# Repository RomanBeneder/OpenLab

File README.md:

</img>

The project OpenLab (an acronym for "Open Laboratory") is located at the Department of Embedded Systems, University of Applied Sciences Technikum Wien. It deals with the development of dedicated lecture notes, demo examples, open source measurement equipment, scripts and other course materials as well as prototype and test environments, in order to provide students low-cost, powerful measurement equipment.

The project is financed by public funds of MA23 City of Vienna, under grant number MA23-Projekt 17-08. The duration of the project is from April 2015 to March 2018.

</img>
</img>

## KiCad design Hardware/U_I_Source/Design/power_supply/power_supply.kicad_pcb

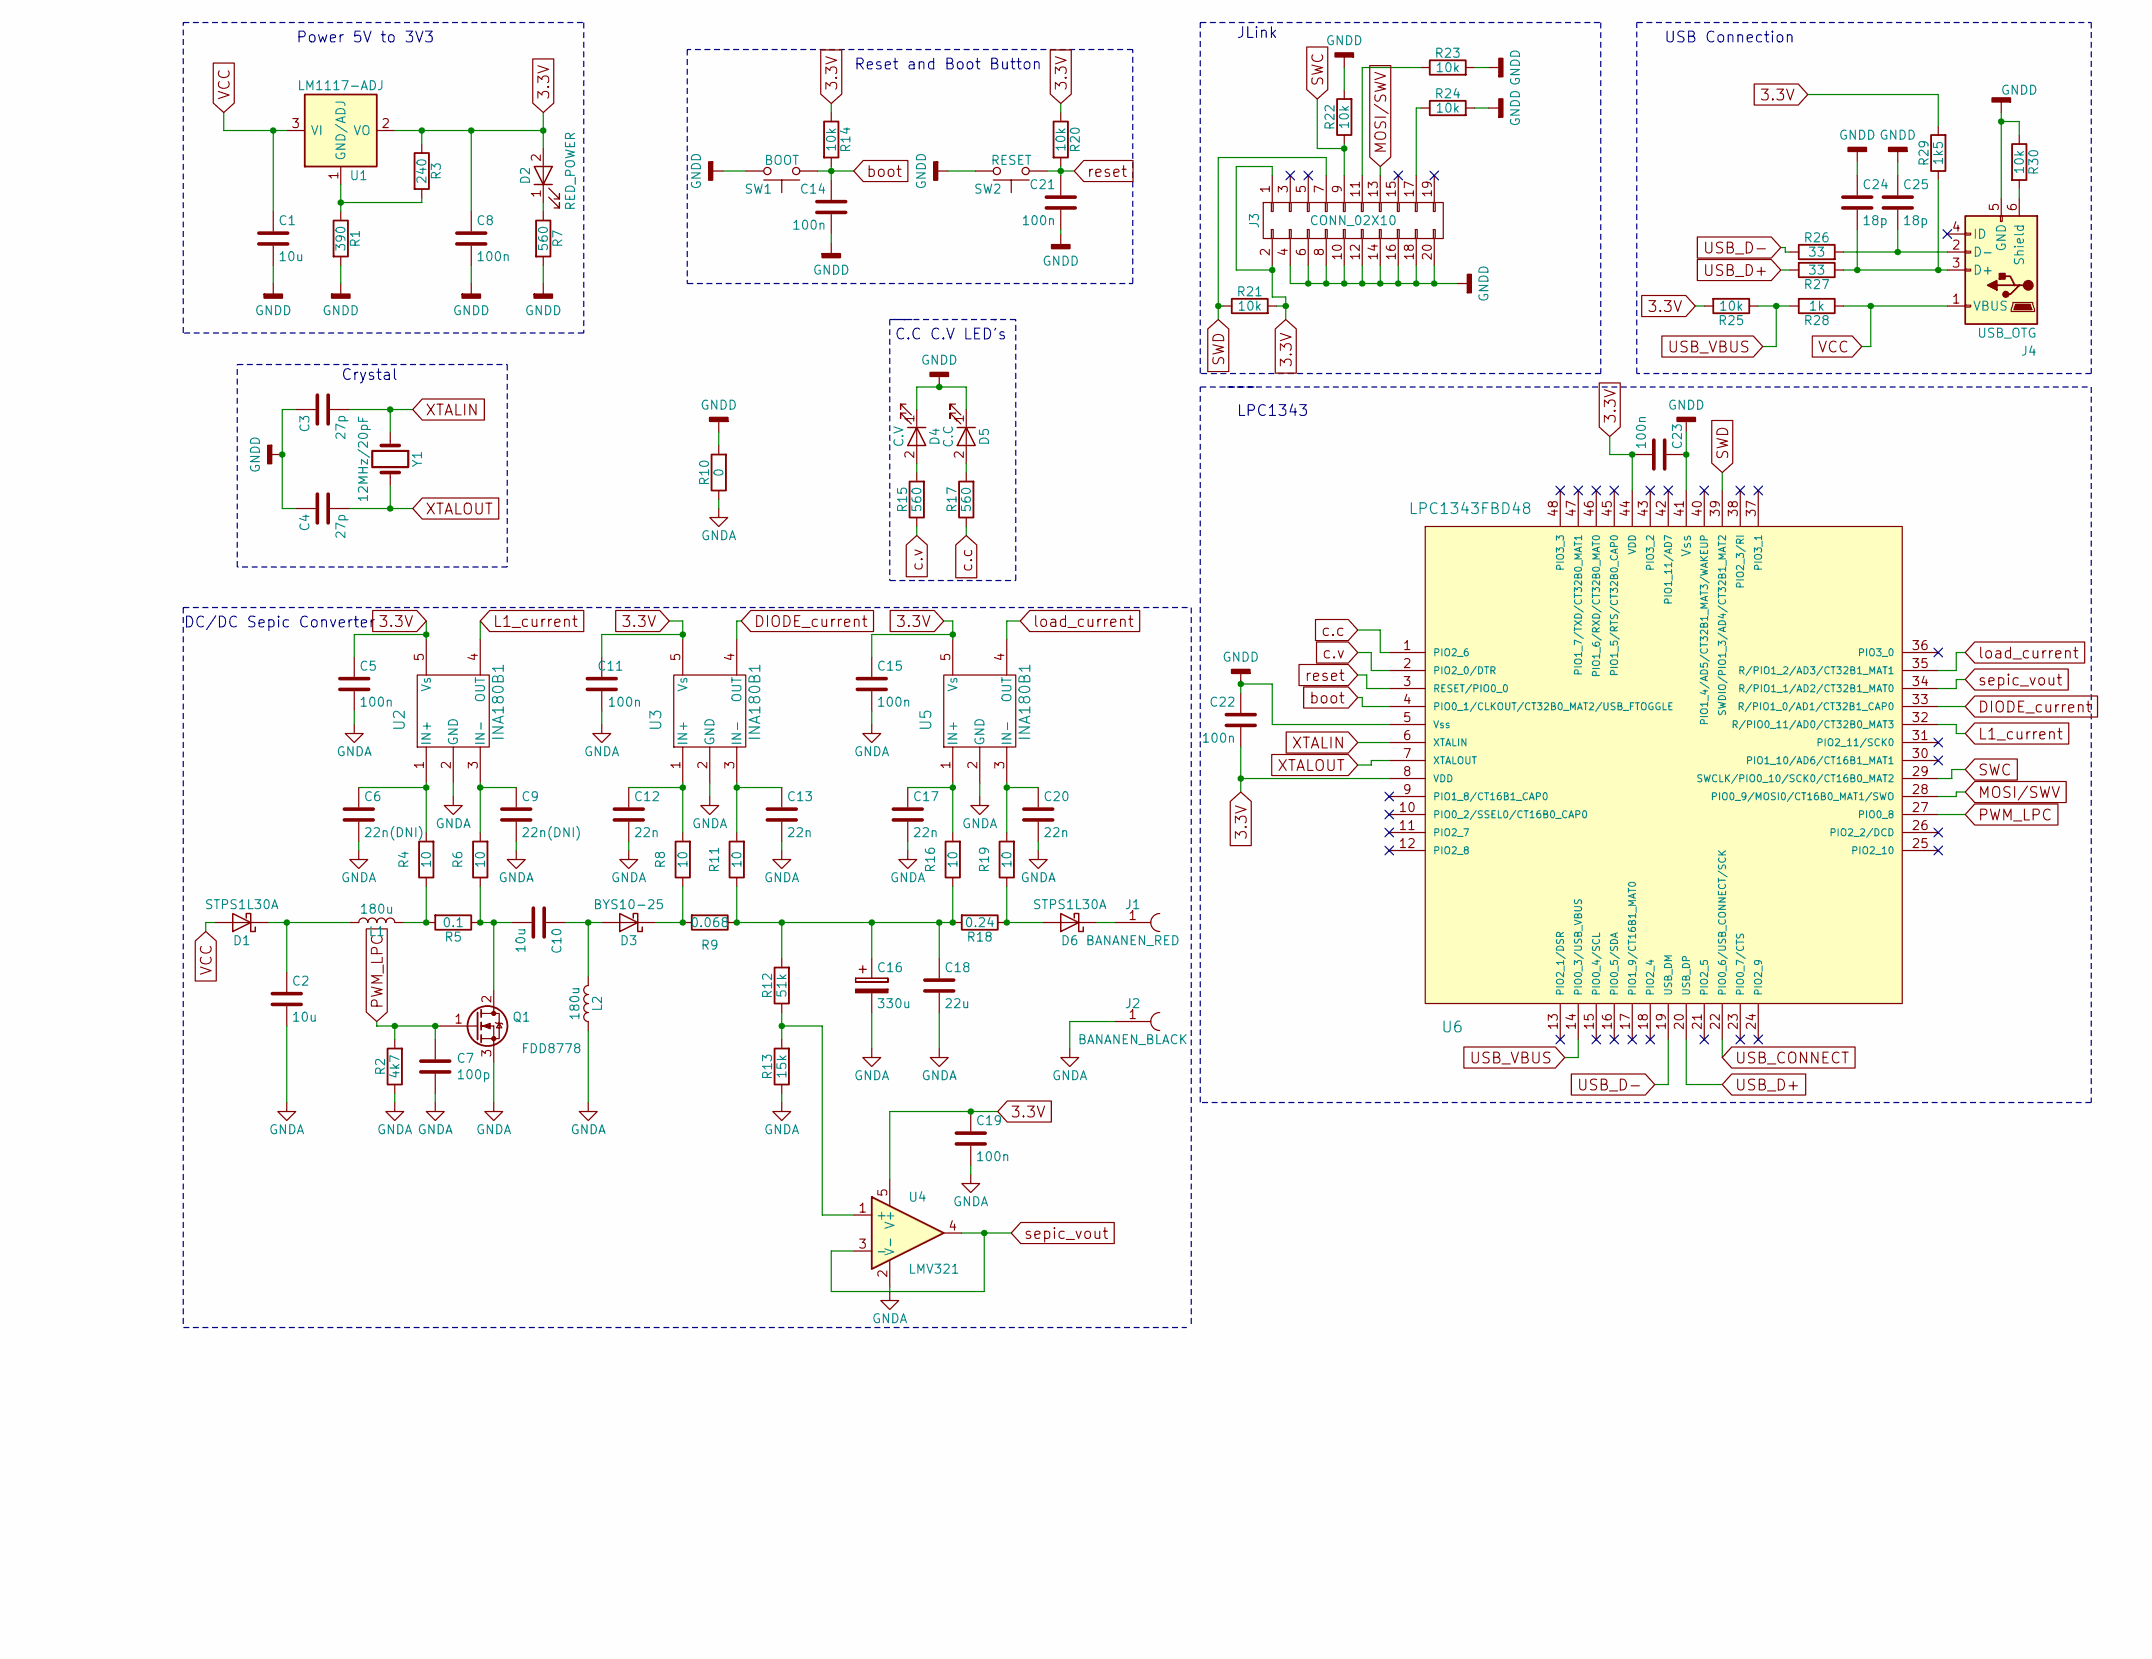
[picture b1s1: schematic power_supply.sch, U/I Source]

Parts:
C1, C2, C10: 10u; C_1206_HandSoldering
C3, C4: 27p; C_0603_HandSoldering
C5, C8, C11, C14, C15, C19, C21, C22, C23: 100n; C_0603_HandSoldering
C6, C9: 22n(DNI); C_0603
C7: 100p; C_0603_HandSoldering
C12, C13, C17, C20: 22n; C_0603
C16: 330u; CP_Elec_10x10
C18: 22u; C_1206_HandSoldering
C24, C25: 18p; C_0603_HandSoldering
D1, D6: STPS1L30A; D_SMA
D2: RED_POWER; LED_PLCC-2
D3: BYS10-25; D_SMA
D4: C.V; LED_PLCC-2
D5: C.C; LED_PLCC-2
J1: BANANEN_RED; Banana_multicomp_4mm
J2: BANANEN_BLACK; Banana_multicomp_4mm
J3: CONN_02X10; Multicomp_MC9A12-2034_2x10x2.54mm_Straight
J4: USB_OTG; USB_Micro-B_SMD
L1, L2: 180u; L_12x12mm_h8mm
Q1: FDD8778; TO-252-2
R1: 390; R_0805_HandSoldering
R2: 4k7; R_0603
R3: 240; R_0805_HandSoldering
R4, R6, R8, R11, R16, R19: 10; R_0805
R5: 0.1; R_1206_HandSoldering
R7, R15, R17: 560; R_0805_HandSoldering
R9: 0.068; R_1206_HandSoldering
R10: 0; R_0805_HandSoldering
R12: 51k; R_0805_HandSoldering
R13: 15k; R_0805_HandSoldering
R14, R20, R21, R22, R23, R24, R25, R30: 10k; R_0805_HandSoldering
R18: 0.24; R_1206_HandSoldering
R26, R27: 33; R_0805_HandSoldering
R28: 1k; R_0805_HandSoldering
R29: 1k5; R_0805_HandSoldering
SW1: BOOT; SW_SPST_KMR2
SW2: RESET; SW_SPST_KMR2
U1: LM1117-ADJ; SOT-223
U2, U3, U5: INA180B1; SOT-23-5_HandSoldering
U4: LMV321; SOT-23-5_HandSoldering
U6: LPC1343FBD48; LQFP-48_7x7mm_Pitch0.5mm
Y1: 12MHz/20pF; Crystal_SMD_HC49-SD

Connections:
3.3V: C5.1, C8.1, C11.2, C15.1, C19.1, C22.2, C23.2, D2.2 (A), J3.1, J3.2, R3.1, R14.1, R20.1, R21.2, R25.2, R29.2, U1.2 (VO), U1.4 (VO), U2.5 (Vs), U3.5 (Vs), U4.5 (V+), U5.5 (Vs), U6.8 (VDD), U6.44 (VDD)
DIODE_current: U3.4 (OUT), U6.33 (R/PIO1_0/AD1/CT32B1_CAP0)
GNDD: C1.2, C3.1, C4.1, C8.2, C14.2, C21.2, C22.1, C23.1, C24.1, C25.1, D4.1 (K), D5.1 (K), J3.4, J3.6, J3.8, J3.10, J3.12, J3.14, J3.16, J3.18, J3.20, J4.5 (GND), R1.2, R7.2, R10.2, R22.2, R23.2, R24.2, R30.1, SW1.2, SW2.2, U6.5 (Vss), U6.41 (Vss)
L1_current: U2.4 (OUT), U6.32 (R/PIO0_11/AD0/CT32B0_MAT3)
MOSI/SWV: J3.13, U6.28 (PIO0_9/MOSI0/CT16B0_MAT1/SWO)
unnamed: C2.1, D1.1 (K), L1.1
unnamed: C6.1, R4.2, U2.1 (IN+)
unnamed: C9.1, R6.2, U2.3 (IN-)
unnamed: C10.1, D3.2 (A), L2.2
unnamed: C10.2, Q1.2 (D), R5.1, R6.1
unnamed: C12.1, R8.2, U3.1 (IN+)
unnamed: C13.1, R11.2, U3.3 (IN-)
unnamed: C16.1, C18.1, R9.1, R11.1, R12.2, R16.1, R18.2
unnamed: C17.1, R16.2, U5.1 (IN+)
unnamed: C20.1, R19.2, U5.3 (IN-)
unnamed: C24.2, J4.3 (D+), R27.1, R29.1
unnamed: C25.2, J4.2 (D-), R26.2
unnamed: D2.1 (K), R7.1
unnamed: D3.1 (K), R8.1, R9.2
unnamed: D4.2 (A), R15.2
unnamed: D5.2 (A), R17.2
unnamed: D6.1 (K), J1.1
unnamed: D6.2 (A), R18.1, R19.1
unnamed: J3.11, R23.1
unnamed: J3.17, R24.1
unnamed: J4.6 (Shield), R30.2
unnamed: L1.2, R4.1, R5.2
unnamed: R1.1, R3.2, U1.1 (GND/ADJ)
unnamed: R12.1, R13.2, U4.1 (+)
PWM_LPC: C7.1, Q1.1 (G), R2.2, U6.27 (PIO0_8)
SWC: J3.9, R22.1, U6.29 (SWCLK/PIO0_10/SCK0/CT16B0_MAT2)
SWD: J3.7, R21.1, U6.39 (SWDIO/PIO1_3/AD4/CT32B1_MAT2)
USB_D+: R27.2, U6.20 (USB_DP)
USB_D-: R26.1, U6.19 (USB_DM)
USB_VBUS: R25.1, R28.2, U6.14 (PIO0_3/USB_VBUS)
VCC: C1.1, D1.2 (A), J4.1 (VBUS), R28.1, U1.3 (VI)
XTALIN: C3.2, U6.6 (XTALIN), Y1.1
XTALOUT: C4.2, U6.7 (XTALOUT), Y1.2
boot: C14.1, R14.2, SW1.1, U6.4 (PIO0_1/CLKOUT/CT32B0_MAT2/USB_FTOGGLE)
c.c: R17.1, U6.1 (PIO2_6)
c.v: R15.1, U6.2 (PIO2_0/DTR)
load_current: U5.4 (OUT), U6.35 (R/PIO1_2/AD3/CT32B1_MAT1)
reset: C21.1, R20.2, SW2.1, U6.3 (RESET/PIO0_0)

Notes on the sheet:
Power 5V to 3V3
DC/DC Sepic Converter
Crystal
Reset and Boot Button
C.C C.V LED's
JLink
USB Connection
LPC1343

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
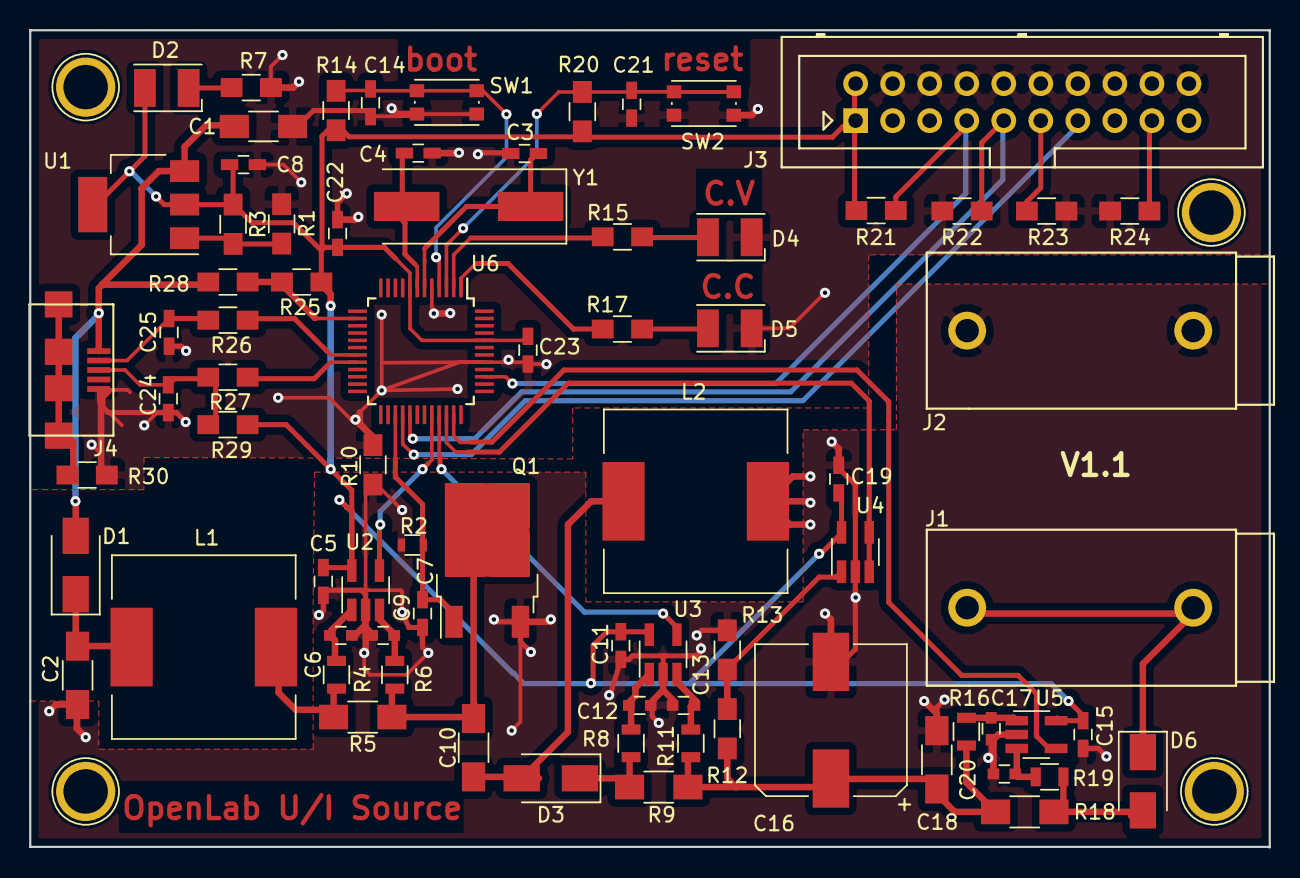
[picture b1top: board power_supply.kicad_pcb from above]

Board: 2 copper layers, 85.0 x 56.0 mm, 77 parts (0 on the bottom side), 45 nets.

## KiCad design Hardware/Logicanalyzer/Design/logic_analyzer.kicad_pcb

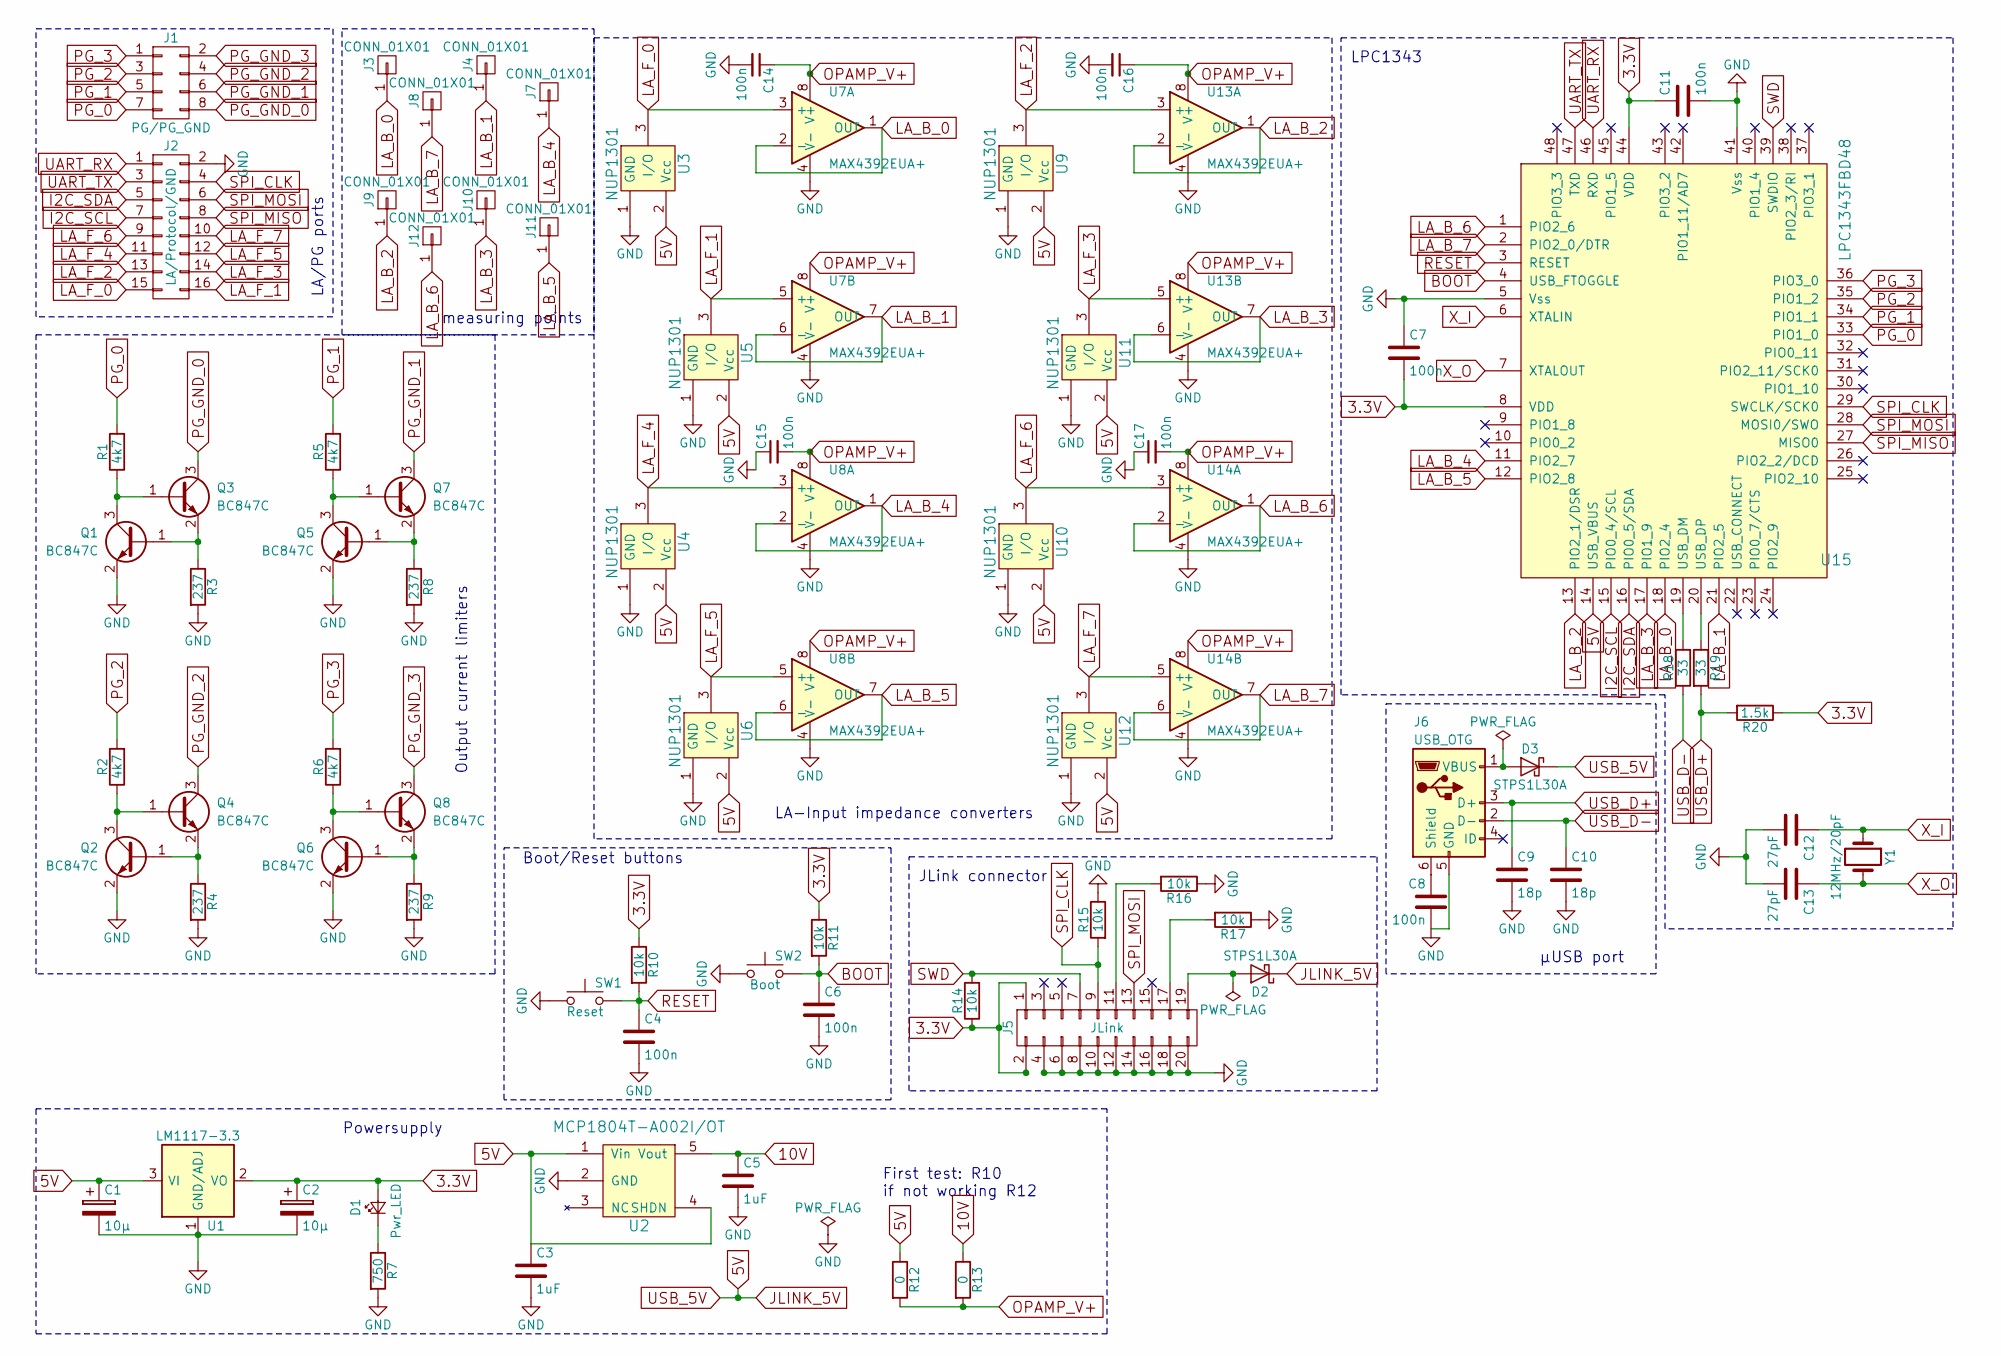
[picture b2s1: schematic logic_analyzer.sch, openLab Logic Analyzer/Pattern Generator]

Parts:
C1, C2: 10µ; C_1206
C3, C5: 1uF; C_0805
C4, C6, C7, C8, C11, C14, C15, C16, C17: 100n; C_0402
C9, C10: 18p; C_0603
C12, C13: 27pF; C_0603
D1: Pwr_LED; LED_PLCC-2
D2, D3: STPS1L30A; D_SMA
J1: PG/PG_GND; Pin_Header_Angled_2x04_Pitch2.54mm
J2: LA/Protocol/GND; Pin_Header_Angled_2x08_Pitch2.54mm
J3, J4, J7, J8, J9, J10, J11, J12: CONN_01X01; Pin_Header_Straight_1x01_Pitch2.54mm
J5: JLink; Multicomp_MC9A12-2034_2x10x2.54mm_Straight
J6: USB_OTG; USB_Micro-B_10103594-0001LF
Q1, Q2, Q3, Q4, Q5, Q6, Q7, Q8: BC847C; SOT-23
R1, R2, R5, R6: 4k7; R_0805
R3, R4, R8, R9: 237; R_0603
R7: 750; R_0603
R10, R11, R14, R15, R16, R17: 10k; R_0402
R12, R13: 0; R_2010_HandSoldering
R18, R19: 33; R_0402
R20: 1.5k; R_0805
SW1: Reset; SW_SPST_KMR2
SW2: Boot; SW_SPST_KMR2
U1: LM1117-3.3; SOT-223
U2: MCP1804T-A002I/OT; SOT-23-5
U3, U4, U5, U6, U9, U10, U11, U12: NUP1301; SOT-23
U7, U8, U13, U14: MAX4392EUA+; uMAX-8
U15: LPC1343FBD48; LQFP-48_7x7mm_Pitch0.5mm
Y1: 12MHz/20pF; Crystal_SMD_HC49-SD

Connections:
3.3V: C2.1, C7.2, C11.1, D1.2 (A), J5.1, J5.2, R10.1, R11.1, R14.1, R20.1, U1.2 (VO), U1.4 (VO), U15.8 (VDD), U15.44 (VDD)
5V: C1.1, C3.1, D2.1 (K), D3.1 (K), R12.1, U1.3 (VI), U2.1 (Vin), U2.4 (SHDN), U3.2 (Vcc), U4.2 (Vcc), U5.2 (Vcc), U6.2 (Vcc), U9.2 (Vcc), U10.2 (Vcc), U11.2 (Vcc), U12.2 (Vcc), U15.14 (USB_VBUS)
10V: C5.1, R13.1, U2.5 (Vout)
BOOT: C6.1, R11.2, SW2.2, U15.4 (USB_FTOGGLE)
GND: C1.2, C2.2, C3.2, C4.2, C5.2, C6.2, C7.1, C8.2, C9.2, C10.2, C11.2, C12.2, C13.2, C14.2, C15.1, C16.2, C17.1, J2.2, J5.4, J5.6, J5.8, J5.10, J5.12, J5.14, J5.16, J5.18, J5.20, J6.5 (GND), Q1.2 (E), Q2.2 (E), Q5.2 (E), Q6.2 (E), R3.2, R4.2, R7.2, R8.2, R9.2, R15.1, R16.1, R17.1, SW1.1, SW2.1, U1.1 (GND/ADJ), U2.2 (GND), U3.1 (GND), U4.1 (GND), U5.1 (GND), U6.1 (GND), U7.4 (V-), U8.4 (V-), U9.1 (GND), U10.1 (GND), U11.1 (GND), U12.1 (GND), U13.4 (V-), U14.4 (V-), U15.5 (Vss), U15.41 (Vss)
I2C_SCL: J2.7, U15.15 (PIO0_4/SCL)
I2C_SDA: J2.5, U15.16 (PIO0_5/SDA)
LA_B_0: J3.1, U7.1 (OUT), U7.2 (-), U15.18 (PIO2_4)
LA_B_1: J4.1, U7.6 (-), U7.7 (OUT), U15.21 (PIO2_5)
LA_B_2: J9.1, U13.1 (OUT), U13.2 (-), U15.13 (PIO2_1/DSR)
LA_B_3: J10.1, U13.6 (-), U13.7 (OUT), U15.17 (PIO1_9)
LA_B_4: J7.1, U8.1 (OUT), U8.2 (-), U15.11 (PIO2_7)
LA_B_5: J11.1, U8.6 (-), U8.7 (OUT), U15.12 (PIO2_8)
LA_B_6: J12.1, U14.1 (OUT), U14.2 (-), U15.1 (PIO2_6)
LA_B_7: J8.1, U14.6 (-), U14.7 (OUT), U15.2 (PIO2_0/DTR)
LA_F_0: J2.15, U3.3 (I/O), U7.3 (+)
LA_F_1: J2.16, U5.3 (I/O), U7.5 (+)
LA_F_2: J2.13, U9.3 (I/O), U13.3 (+)
LA_F_3: J2.14, U11.3 (I/O), U13.5 (+)
LA_F_4: J2.11, U4.3 (I/O), U8.3 (+)
LA_F_5: J2.12, U6.3 (I/O), U8.5 (+)
LA_F_6: J2.9, U10.3 (I/O), U14.3 (+)
LA_F_7: J2.10, U12.3 (I/O), U14.5 (+)
unnamed: C8.1, J6.6 (Shield)
unnamed: D1.1 (K), R7.1
unnamed: D2.2 (A), J5.19
unnamed: D3.2 (A), J6.1 (VBUS)
unnamed: J5.11, R16.2
unnamed: J5.17, R17.2
unnamed: Q1.1 (B), Q3.2 (E), R3.1
unnamed: Q1.3 (C), Q3.1 (B), R1.1
unnamed: Q2.1 (B), Q4.2 (E), R4.1
unnamed: Q2.3 (C), Q4.1 (B), R2.1
unnamed: Q5.1 (B), Q7.2 (E), R8.1
unnamed: Q5.3 (C), Q7.1 (B), R5.1
unnamed: Q6.1 (B), Q8.2 (E), R9.1
unnamed: Q6.3 (C), Q8.1 (B), R6.1
unnamed: R18.2, U15.19 (USB_DM)
unnamed: R19.1, U15.20 (USB_DP)
OPAMP_V+: C14.1, C15.2, C16.1, C17.2, R12.2, R13.2, U7.8 (V+), U8.8 (V+), U13.8 (V+), U14.8 (V+)
PG_0: J1.7, R1.2, U15.33 (PIO1_0)
PG_1: J1.5, R5.2, U15.34 (PIO1_1)
PG_2: J1.3, R2.2, U15.35 (PIO1_2)
PG_3: J1.1, R6.2, U15.36 (PIO3_0)
PG_GND_0: J1.8, Q3.3 (C)
PG_GND_1: J1.6, Q7.3 (C)
PG_GND_2: J1.4, Q4.3 (C)
PG_GND_3: J1.2, Q8.3 (C)
RESET: C4.1, R10.2, SW1.2, U15.3 (RESET)
SPI_CLK: J2.4, J5.9, R15.2, U15.29 (SWCLK/SCK0)
SPI_MISO: J2.8, U15.27 (MISO0)
SPI_MOSI: J2.6, J5.13, U15.28 (MOSI0/SWO)
SWD: J5.7, R14.2, U15.39 (SWDIO)
UART_RX: J2.1, U15.46 (RXD)
UART_TX: J2.3, U15.47 (TXD)
USB_D+: C9.1, J6.3 (D+), R19.2, R20.2
USB_D-: C10.1, J6.2 (D-), R18.1
X_I: C12.1, U15.6 (XTALIN), Y1.1
X_O: C13.1, U15.7 (XTALOUT), Y1.2

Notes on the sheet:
First test: R10 if not working R12
LPC1343
JLink connector
LA-Input impedance converters
µUSB port
LA/PG ports
Output current limiters
Powersupply
Boot/Reset buttons
measuring points

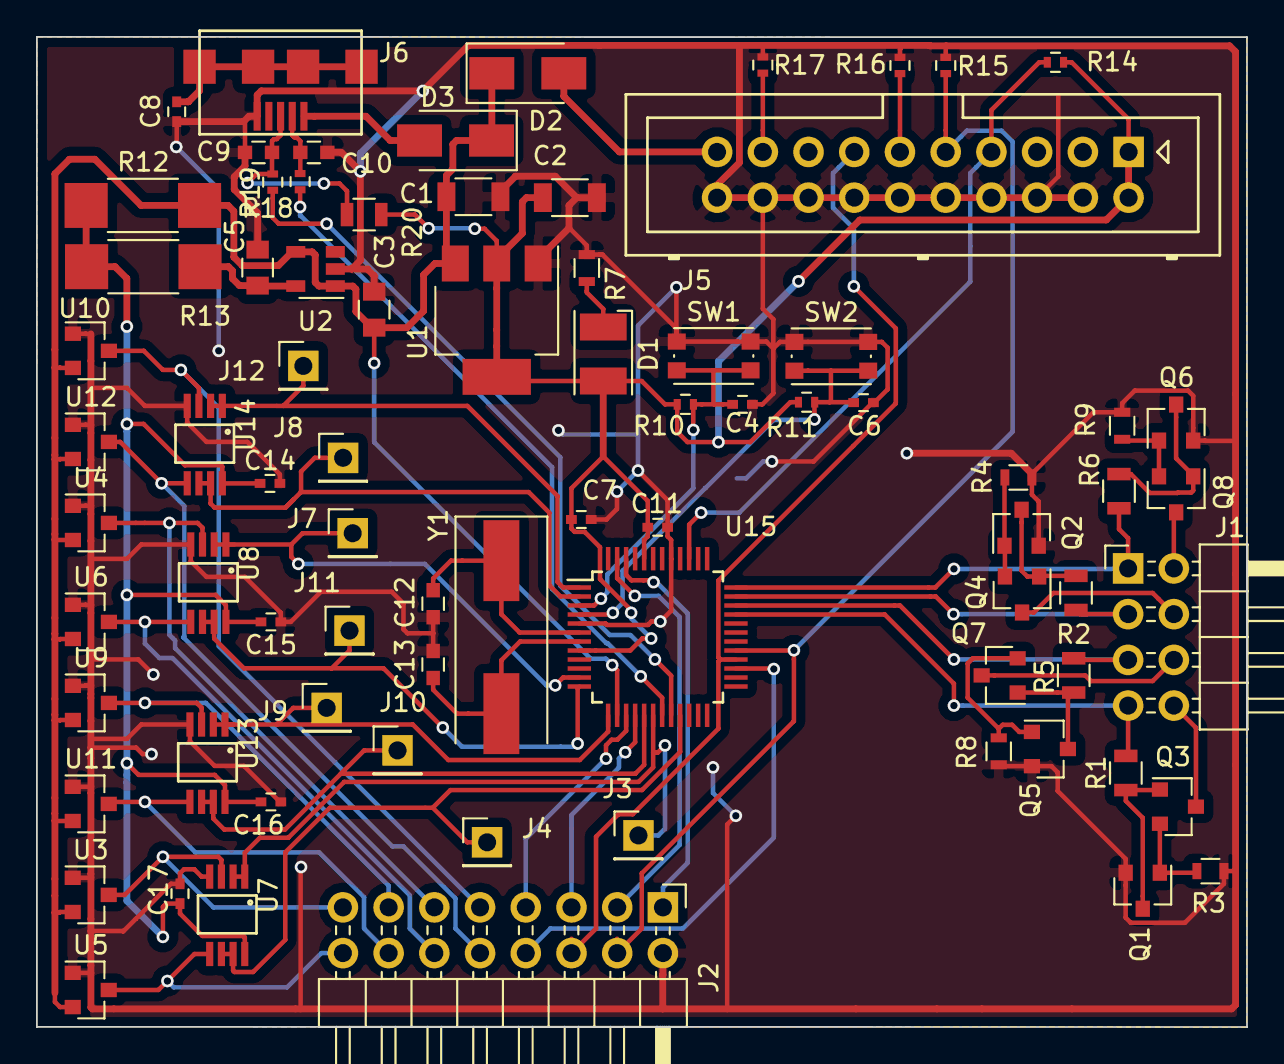
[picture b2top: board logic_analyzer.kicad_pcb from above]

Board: 2 copper layers, 67.2 x 55.0 mm, 78 parts (0 on the bottom side), 59 nets.

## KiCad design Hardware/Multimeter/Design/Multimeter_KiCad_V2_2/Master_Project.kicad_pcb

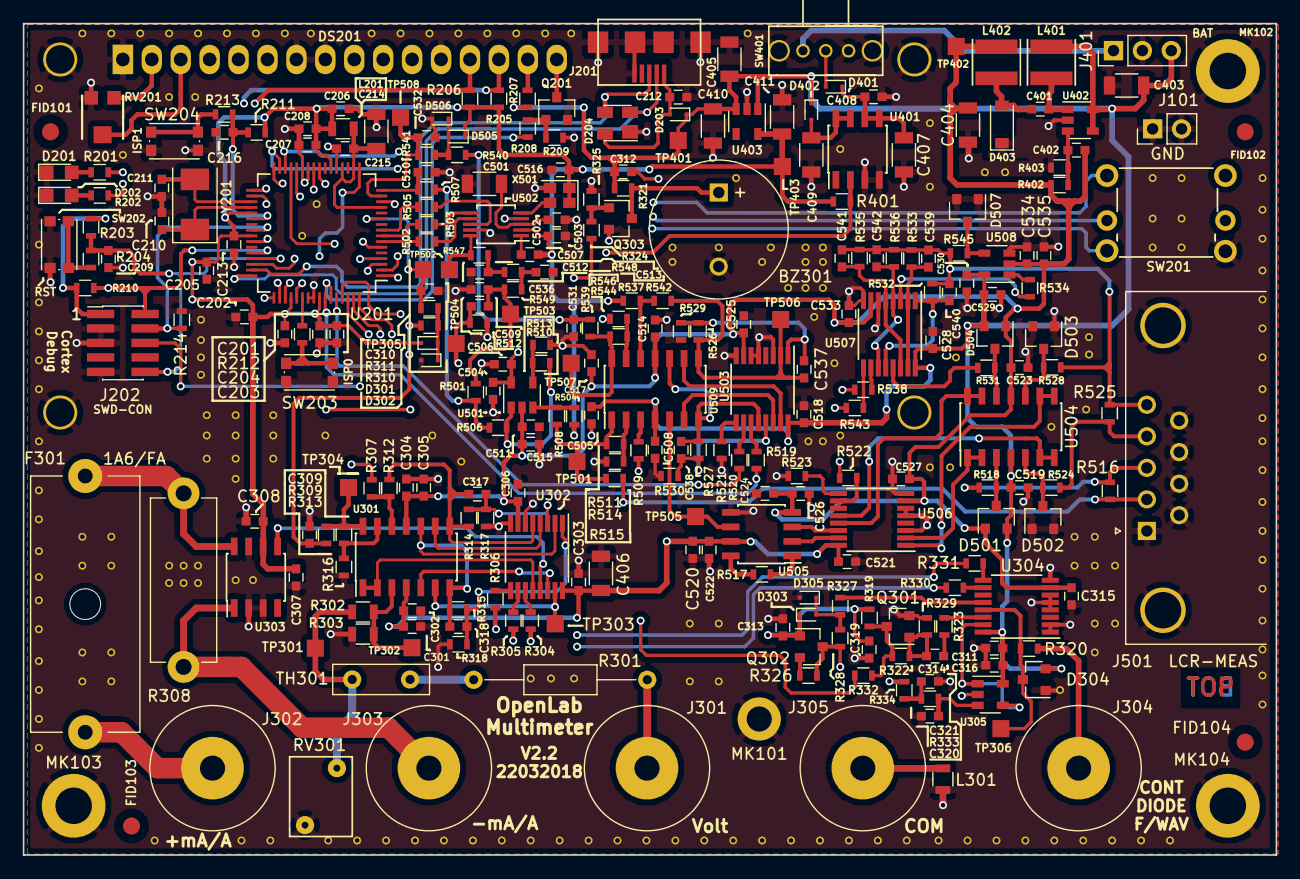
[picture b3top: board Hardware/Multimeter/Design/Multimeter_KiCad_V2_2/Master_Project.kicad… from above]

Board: 4 copper layers, 110.0 x 73.0 mm, 283 parts (0 on the bottom side), 166 nets.

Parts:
BZ301: Buzzer; MagneticBuzzer_ProSignal_ABT-410-RC
C201, C203, C205, C207, C212, C213, C507: 10n; C_0603
C202, C204, C206, C208, C209, C214, C216, C302, C303, C304, C306, C308, C310, C311, C312, C313, C315, C316, C317, C318, C319, C408, C502, C503, C506, C508, C511, C514, C516, C518, C519, C521, C522, C523, C524, C525, C527, C528, C530, C533, C534: µ1; C_0603
C210, C211: 18p; C_0603
C215, C405, C406, C407, C410, C501: 10µ; C_1206
C301, C305, C307, C314, C504, C505, C509, C515, C517, C520, C526, C529, C535: 2µ2; C_0603
C309, C401: 1µ; C_0603
C320, C321: *; C_0603
C402: 1n2; C_0603
C403, C404: 22µ; C_1206
C409: 4µ7; C_1206
C411: 2µ2; C_1206
C510, C512, C513, C532, C536, C540: 1n; C_0603
C531: n.p.; C_0603
C537, C538: 22p; C_0603
C539: 47p; C_0603
C541: 470p; C_0603
C542: 10p; C_0603
D201: PWR_GN; LED_0805
D202: ERR_RED; LED_0805
D203, D301, D302, D303, D305, D401, D402, D505, D506: DB27308; D_SC-80
D204: PRTR5V0U2X; SOT-143
D304, D501, D502, D503, D504, D507: BAV199; SOT-23
D403: MBR0520; D_SOD-123
DS201: MC21605C6W; WC1602A
F301: HRC_1A6; Fuseholder5x20_horiz_open_Schurter_0031_8201
FID101, FID102, FID103, FID104: Fiducial; Fiducial_1.5mm_Dia_2.54mm_Outer_CopperTop
J101: Conn_01x02; Pin_Header_Straight_1x02_Pitch2.54mm
J201: USB_OTG; USB_Micro_B
J202: SWD CON; Pin_Header_Straight_2x05_Pitch1.27mm_SMD
J301: V; Banana_Jack_1Pin
J302: + mA/A; Banana_Jack_1Pin
J303: - mA/A; Banana_Jack_1Pin
J304: D/T/WAV; Banana_Jack_1Pin
J305: COM; Banana_Jack_1Pin
J401: EXT_PS; Pin_Header_Straight_1x03_Pitch2.54mm
J501: LCR_Meas_Jack; DSUB-9_Male_Horizontal_P2.77x2.84mm_EdgePinOffset7.70mm_Hou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
L201, L301: FB; R_0805
L401, L402: 22µ; Inductor_Taiyo-Yuden_MD-4040
MK101: MH_PAD; MountingHole_2.2mm_M2_DIN965_Pad
MK102, MK103, MK104: MH_PAD; MountingHole_3.2mm_M3_DIN965_Pad
Q201: BC818; SOT-23
Q301, Q303: BC818-40; SOT-23
Q302: MMBFJ112; SOT-23
R201, R202, R310, R323, R326, R535, R540: 1k; R_0603
R203, R208, R210, R211, R214, R307, R312, R313, R316, R324, R401, R403, R508, R510, R533, R542, R544: 10k; R_0603
R204, R212, R213, R309, R327, R328, R507, R515, R516, R518, R524, R525, R528, R531, R532, R545: 100; R_0603
R205, R206: 2k2; R_0603
R207: 150; R_0603
R209, R325, R512, R536: 100k; R_0603
R301: 1E; R_Axial_DIN0207_L6.3mm_D2.5mm_P15.24mm_Horizontal
R302: 1M; R_0805
R303: 71k5; R_0805
R304, R305, R306, R321, R330, R331, R502, R503, R505, R519, R520, R521, R522, R523, R534, R538, R543: 56; R_0603
R308: 0.01; R_Axial_DIN0614_L14.3mm_D5.7mm_P15.24mm_Horizontal
R311, R319, R332, R541: 470; R_0603
R314, R315, R526, R527: 18k; R_0603
R317, R318, R529, R530: 2k; R_0603
R320, R506, R509, R511, R539: 0; R_0603
R322: 33k; R_0603
R329, R501, R514: n.p.; R_0603
R333, R334: *; R_0603
R402: 29k4; R_0603
R504, R513, R537, R546: 20k; R_0603
R517: 48k7; R_0603
R547, R548, R549: 33; R_0603
RV201: 10k; Potentiometer_SMD_OpenLab
RV301: Varistor; RV_Disc_D7_W5.5_P5
SW201: NavigationSwitch; SKQUCAA010_SKQU_5_Polig_ALPS
SW202, SW203, SW204: SW_Push; SW_SPST_KMR2
SW401: SW_SPDT_OpenLab; SWITCH-2-WAY_SPDT
TH301: Thermistor_PTC; R_Box_L14.4mm_W2.5mm_P5.08mm
TP301, TP302, TP303, TP304, TP305, TP306, TP501, TP502, TP503, TP504, TP505, TP506, TP507, TP508: TEST; Measurement_Point_Square-SMD-Pad_Small
TP401: +5V; Measurement_Point_Square-SMD-Pad_Small
TP402: -5V; Measurement_Point_Square-SMD-Pad_Small
TP403: +3V3; Measurement_Point_Square-SMD-Pad_Small
U201: LPC1549; LQFP-64_10x10mm_Pitch0.5mm
U301, U504, U509: MAX44252; SOIC-14_3.9x8.7mm_Pitch1.27mm
U302, U503, U506: 74HCT4053; TSSOP-16_4.4x5mm_Pitch0.65mm
U303: INA286; SOIC-8_3.9x4.9mm_Pitch1.27mm
U304, U507: 74HCT4052; TSSOP-16_4.4x5mm_Pitch0.65mm
U305, U501, U508: MAX44250; SOT-23-5
U401: TPS76550D; SOIC-8_3.9x4.9mm_Pitch1.27mm
U402: LT1611; SOT-23-5
U403: LP2981-N; SOT-23-5
U502: AD9833; MSOP-10_3x3mm_Pitch0.5mm
U505: INA129; SOIC-8_3.9x4.9mm_Pitch1.27mm
X501: 25MHz; Oscillator_SMD_SeikoEpson_SG210-4pin_2.5x2.0mm
Y201: 12MHz; Crystal_SMD_0603-2pin_6.0x3.5mm

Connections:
+3V3: C201.2, C202.2, C203.2, C204.2, C205.2, C206.2, C207.2, C208.2, C213.2, C307.1, C308.1, C313.1, C319.1, C411.1, C503.1, C507.2, C516.2, D301.1, D303.1, D505.1, J202.1, L201.1, Q302.1, R203.2, R205.2, R206.2, R210.2, R211.1, R319.1, R401.1, R504.2, R537.2, TP403.1, U201.22, U201.37, U201.41, U201.52, U201.57, U303.6, U403.5, U502.2, X501.1, X501.4
+5V: C301.1, C302.1, C303.1, C311.1, C312.1, C316.1, C403.1, C405.1, C406.1, C410.1, C504.1, C505.1, C506.1, C508.1, C518.1, C519.1, C520.1, C521.1, C522.1, C528.1, C529.1, C530.1, D203.1, D304.2, D402.1, D501.2, D504.2, DS201.2, J401.3, L401.1, R207.1, R321.1, RV201.1, TP401.1, U301.4, U302.16, U304.16, U305.5, U402.4, U402.5, U403.1, U403.3, U501.5, U503.16, U504.4, U505.7, U506.16, U507.16, U508.5, U509.4
-5V: C304.1, C305.1, C306.1, C315.1, C402.1, C404.2, C511.1, C514.1, C515.1, C517.1, C523.1, C524.1, C525.1, C526.1, C527.1, C533.1, C534.1, C535.1, D501.1, D504.1, L402.2, R402.1, TP402.1, U301.11, U302.7, U304.7, U501.2, U503.7, U504.11, U505.4, U506.7, U507.7, U508.2, U509.11
/MCU Signal Processing/DISP_BACK_LIGHT_A: DS201.15, R207.2
/MCU Signal Processing/DISP_BACK_LIGHT_CTRL: R208.2, U201.59
/MCU Signal Processing/DISP_BACK_LIGHT_K: DS201.16, Q201.3
/MCU Signal Processing/MCU_~RESET~: C209.2, J202.10, R203.1, R204.2, U201.45
/MCU Signal Processing/PIO1_2: SW201.5, U201.25
/MCU Signal Processing/PIO1_3: SW201.6, U201.28
/MCU Signal Processing/PIO1_4: SW201.1, U201.33
/MCU Signal Processing/PIO1_5: SW201.2, U201.34
/MCU Signal Processing/PIO1_6: SW201.3, U201.46
/MCU Signal Processing/PIO1_7_LED_PWR: R201.2, U201.51
/MCU Signal Processing/PIO1_8_LED_ERR: R202.2, U201.53
/MCU Signal Processing/PIO1_9/ISP0: R212.2, U201.54
/MCU Signal Processing/PIO1_11/ISP1: C216.2, R211.2, R213.2, U201.38
/MCU Signal Processing/SWCLK/PIO0_19/TCK: J202.4, R214.2, U201.40
/MCU Signal Processing/SWDIO/PIO0_20/TMS: J202.2, R210.1, U201.44
/MCU Signal Processing/SWO_PIO1_0: J202.6, U201.4
/MT Measurement Tools/CONT_TEST: R327.1, U304.12
/MT Measurement Tools/U/I_Measurement: U301.5, U302.14
/TLD_ADC_MES_SIG: C532.2, R541.1, TP508.1, U201.15
/TLD_ADC_REF_SIG: C510.2, R507.1, U201.16
/TLD_BUZZER: R324.2, U201.2
/TLD_CONT_TST: Q302.3, R326.2, R328.2, U201.3
/TLD_CURR_RG_A: R538.2, U201.30
/TLD_CURR_RG_B: R543.2, U201.31
/TLD_DAC_SIG: R334.2, U201.24
/TLD_DDS_FSYNC: R505.2, U201.9
/TLD_DDS_SCLK: R502.2, U201.7
/TLD_DDS_SDATA: R503.2, U201.8
/TLD_FREQ_TMR: R332.2, U201.1
/TLD_LCR_UI_GAIN_x10: R519.2, U201.58
/TLD_LCR_UI_GAIN_x100: R520.2, U201.60
/TLD_LCR_UI_SEL: R522.2, U201.32
/TLD_MU_PG: R401.2, U201.6, U401.2
/TLD_TOOL_SEL_A: R330.2, U201.62
/TLD_TOOL_SEL_B: R331.2, U201.63
/TLD_UI_GAIN_x10: R305.1, U201.64
/TLD_UI_GAIN_x100: R306.1, U201.61
/TLD_UI_SEL: R304.1, U201.17
/TLD_UI_SIGNAL: C310.2, R311.2, TP305.1, U201.11
/TLD_U_SIGN: R307.1, U201.29
GND: BZ301.2, C201.1, C202.1, C203.1, C204.1, C205.1, C206.1, C207.1, C208.1, C209.1, C210.2, C211.2, C212.1, C213.1, C214.1, C215.1, C216.1, C301.2, C302.2, C303.2, C304.2, C305.2, C306.2, C307.2, C308.2, C309.1, C310.1, C311.2, C312.2, C313.2, C315.2, C316.2, C319.2, C320.1, C321.1, C403.2, C404.1, C405.2, C406.2, C407.2, C408.2, C409.2, C410.2, C411.2, C501.1, C502.1, C503.2, C504.2, C505.2, C506.2, C508.2, C510.1, C511.2, C512.1, C513.1, C514.2, C515.2, C516.1, C517.2, C518.2, C519.2, C520.2, C521.2, C522.2, C523.2, C524.2, C525.2, C526.2, C527.2, C528.2, C529.2, C530.2, C531.1, C532.1, C533.2, C534.2, C535.2, C536.1, D201.1, D202.1, D204.1, D302.2, D304.1, D305.2, D403.1, D502.1, D502.2, D503.1, D503.2, D506.2, D507.1, D507.2, DS201.1, DS201.7, DS201.8, DS201.12, J101.1, J101.2, J201.5, J201.6, J202.3, J202.5, J202.9, J401.2, J501.0, J501.1, J501.6, J501.7, J501.8, J501.9, L301.2, MK101.1, MK102.1, MK103.1, MK104.1, Q201.2, Q301.2, Q303.2, R209.2, R214.1, R303.2, R316.2, R317.2, R318.2, R325.1, R329.2, R403.2, R512.2, R513.2, R514.2, R521.2, R523.2, R529.2, R530.2, R546.2, RV201.3, RV301.2, SW201.4, SW202.1, SW203.1, SW204.1, SW401.3, SW401.4, U201.14, U201.21, U201.26, U201.27, U201.42, U201.55, U201.56, U302.6, U302.8, U303.2, U303.3, U303.7, U304.1, U304.2, U304.4, U304.5, U304.6, U304.8, U305.2, U401.3, U401.4, U402.2, U403.2, U502.4, U502.9, U503.3, U503.5, U503.6, U503.8, U505.5, U506.3, U506.5, U506.6, U506.8, U507.6, U507.8, U508.3, X501.2
unnamed: BZ301.1, Q303.3, R321.2
unnamed: C210.1, U201.36, Y201.1
unnamed: C211.1, U201.35, Y201.2
unnamed: C212.2, D203.2, D204.4, J201.1
unnamed: C214.2, C215.2, L201.2, U201.13, U201.18, U201.20
unnamed: C309.2, R309.2, R310.1
unnamed: C314.1, Q301.1, R322.1, R329.1
unnamed: C314.2, R323.2
unnamed: C317.1, R314.2, R317.1, U302.3
unnamed: C317.2, R312.1, R314.1, U301.8, U302.5
unnamed: C318.1, R315.2, R318.1, U302.1
unnamed: C318.2, R315.1, U301.7, U301.10, U302.2
unnamed: C320.2, R333.1, U305.3
unnamed: C321.2, R333.2, R334.1
unnamed: C401.1, D403.2, L402.1
unnamed: C401.2, L401.2, U402.1
unnamed: C402.2, R402.2, R403.1, U402.3
unnamed: C407.1, C408.1, D401.1, U401.5, U401.6
unnamed: C409.1, D402.2, U401.7, U401.8
unnamed: C501.2, C502.2, U502.3
unnamed: C507.1, U502.1
unnamed: C509.1, C536.2, R501.2, R549.1, TP503.1
unnamed: C509.2, R509.2, R512.1, TP504.1
unnamed: C512.2, R547.1, R548.2
unnamed: C513.2, R548.1, R549.2
unnamed: C531.2, R539.1, R540.2
unnamed: C537.1, R526.2, R529.1, U503.1
unnamed: C537.2, R526.1, R542.2, TP506.1, U503.2, U509.8
unnamed: C538.1, R527.2, R530.1, U503.13
unnamed: C538.2, R527.1, U503.12, U509.7, U509.10
unnamed: C539.1, R533.1, U507.2, U507.15
unnamed: C539.2, C540.2, C541.2, C542.2, J501.5, R525.2, R528.2, R532.2, R533.2, R535.2, R536.2, R545.2
unnamed: C540.1, R532.1, U507.1, U507.12
unnamed: C541.1, R535.1, U507.5, U507.14
unnamed: C542.1, R536.1, U507.4, U507.11
unnamed: D201.2, R201.1
unnamed: D202.2, R202.1
unnamed: D204.2, J201.2, U201.48
unnamed: D204.3, J201.3, U201.47
unnamed: D301.2, D302.1, R310.2, R311.1
unnamed: D303.2, D305.1, R327.2, R328.1
unnamed: D304.3, R320.2, TP306.1, U304.13
unnamed: D401.2, SW401.2
unnamed: D501.3, R518.1, U504.3
unnamed: D502.3, R524.1, U504.5
unnamed: D503.3, R528.1, U504.10
unnamed: D504.3, R531.1, U504.12
unnamed: D505.2, D506.1, R540.1, R541.2
unnamed: D507.3, R545.1, U508.4
unnamed: DS201.3, RV201.2
unnamed: DS201.13, R206.1, U201.50
unnamed: DS201.14, R205.1, U201.49
unnamed: F301.1, R308.1, U303.8
unnamed: F301.2, J302.1
unnamed: J301.1, R301.2
unnamed: J303.1, R308.2, U303.1
unnamed: J304.1, R320.1
unnamed: J305.1, L301.1
unnamed: J401.1, SW401.1
unnamed: J501.2, R515.2, R516.1
unnamed: J501.3, R516.2, R518.2
unnamed: J501.4, R524.2, R525.1
unnamed: Q201.1, R208.1, R209.1
unnamed: Q301.3, R319.2, R322.2, R332.1
unnamed: Q302.2, R326.1
unnamed: Q303.1, R324.1, R325.2
unnamed: R204.1, SW202.2
unnamed: R212.1, SW203.2
unnamed: R213.1, SW204.2
unnamed: R301.1, TH301.2
unnamed: R302.1, R303.1, TP302.1, U301.3
unnamed: R302.2, RV301.1, TH301.1, TP301.1
unnamed: R304.2, U302.11
unnamed: R305.2, U302.10
unnamed: R306.2, U302.9
unnamed: R307.2, R312.2, U301.12
unnamed: R309.1, R313.1, TP304.1, U301.14
unnamed: R313.2, R316.1, U301.13
unnamed: R323.1, U304.14
unnamed: R330.1, U304.10
unnamed: R331.1, U304.9
unnamed: R501.1, R506.1, R507.2
unnamed: R502.1, U502.7
unnamed: R503.1, U502.6
unnamed: R504.1, R508.1, U501.3
unnamed: R505.1, U502.8
unnamed: R506.2, R510.1, U501.1
unnamed: R508.2, R511.1, R515.1, TP501.1, U509.1
unnamed: R509.1, U509.3
unnamed: R510.2, R513.1, U501.4
unnamed: R511.2, R514.1, U509.2
unnamed: R517.1, U505.8
unnamed: R517.2, U505.1
unnamed: R519.1, U503.11
unnamed: R520.1, U503.10
unnamed: R521.1, U503.9
unnamed: R522.1, U506.10, U506.11
unnamed: R523.1, U506.9
unnamed: R531.2, U507.13
unnamed: R534.1, U508.1
unnamed: R534.2, U507.3
unnamed: R537.1, R542.1, U509.12
unnamed: R538.1, U507.10
unnamed: R539.2, R544.1, TP507.1, U509.14
unnamed: R543.1, U507.9
unnamed: R544.2, R546.1, U509.13
unnamed: R547.2, TP502.1, U502.10
unnamed: TP303.1, U301.6, U302.15
unnamed: TP505.1, U505.6, U509.5
unnamed: U301.1, U301.2, U302.12
unnamed: U301.9, U302.4
unnamed: U302.13, U303.5
unnamed: U304.15, U305.1, U305.4
unnamed: U502.5, X501.3
unnamed: U503.14, U509.6
unnamed: U503.15, U509.9
unnamed: U504.1, U504.2, U506.2
unnamed: U504.6, U504.7, U506.12
unnamed: U504.8, U504.9, U506.1
unnamed: U504.13, U504.14, U506.13
unnamed: U505.2, U506.15
unnamed: U505.3, U506.14
